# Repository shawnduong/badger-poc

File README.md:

# badger
Badger is a closed-source IoT RFID-based authentication, attendance tracking, 
notification, and punishmentx system for small to large scale events.

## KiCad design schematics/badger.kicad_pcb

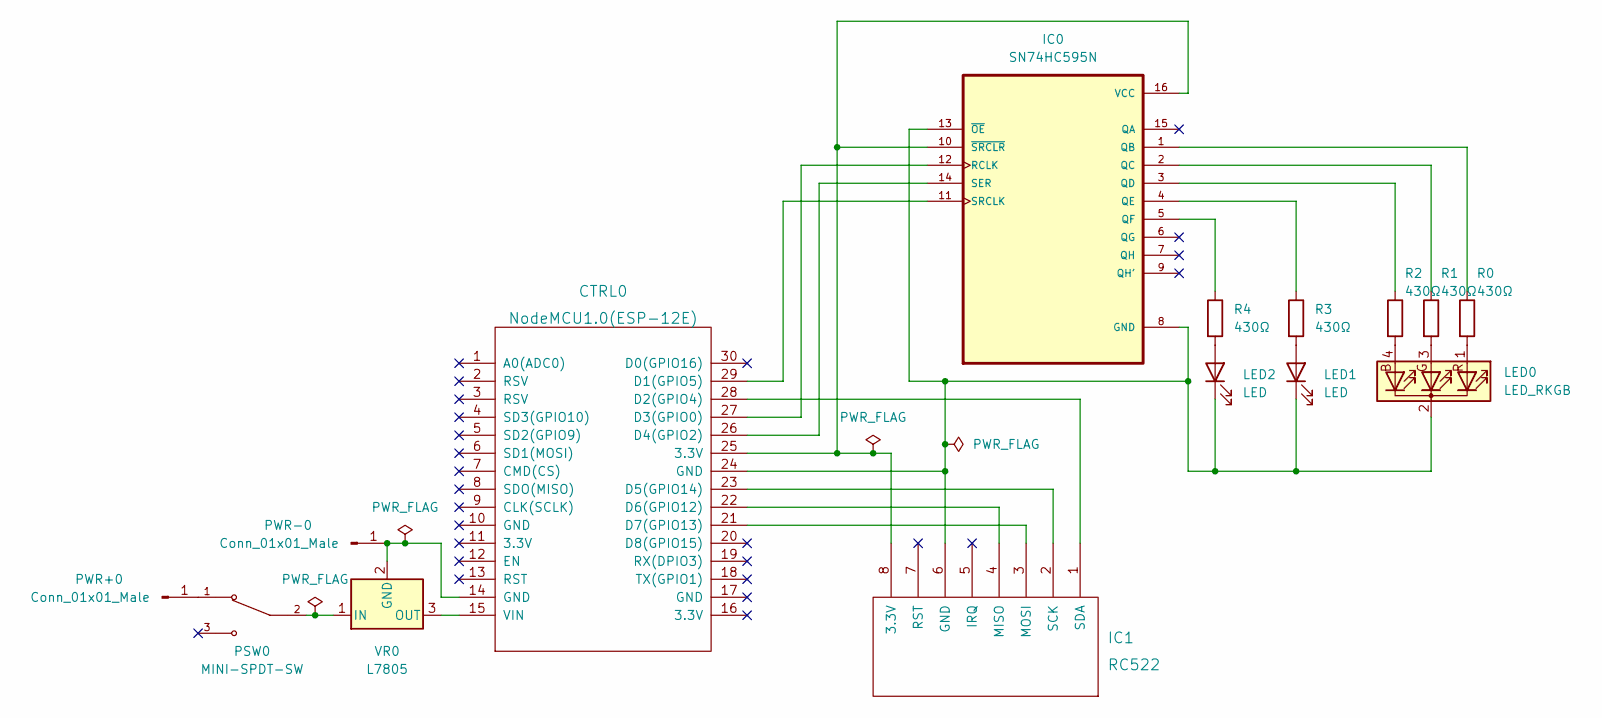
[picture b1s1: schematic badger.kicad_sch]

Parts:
CTRL0: NodeMCU1.0(ESP-12E); NodeMCU-LoLinV3
IC0: SN74HC595N; DIP794W45P254L1969H508Q16
IC1: RC522; rfid-rc522
LED0: LED_RKGB; LED_D5.0mm-4_RGB_Wide_Pins
LED1, LED2: LED; LED_D5.0mm
PSW0: MINI-SPDT-SW; SW_MINI-SPDT-SW; PARTREV C
PWR+0: Conn_01x01_Male; TestPoint_Pad_D2.0mm
PWR-0: Conn_01x01_Male; TestPoint_Pad_D2.0mm
R0, R1, R2, R3, R4: 430Ω; R_Axial_DIN0204_L3.6mm_D1.6mm_P7.62mm_Horizontal
VR0: L7805; TO-220-3_Vertical

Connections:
unnamed: CTRL0.14 (GND), PWR-0.1, VR0.2 (GND)
unnamed: CTRL0.15 (VIN), VR0.3 (OUT)
unnamed: CTRL0.21 (D7(GPIO13)), IC1.3 (MOSI)
unnamed: CTRL0.22 (D6(GPIO12)), IC1.4 (MISO)
unnamed: CTRL0.23 (D5(GPIO14)), IC1.2 (SCK)
unnamed: CTRL0.24 (GND), IC0.8 (GND), IC0.13 (~OE), IC1.6 (GND), LED0.2 (K), LED1.1 (K), LED2.1 (K)
unnamed: CTRL0.25 (3.3V), IC0.10 (~SRCLR), IC0.16 (VCC), IC1.8 (3.3V)
unnamed: CTRL0.26 (D4(GPIO2)), IC0.14 (SER)
unnamed: CTRL0.27 (D3(GPIO0)), IC0.12 (RCLK)
unnamed: CTRL0.28 (D2(GPIO4)), IC1.1 (SDA)
unnamed: CTRL0.29 (D1(GPIO5)), IC0.11 (SRCLK)
unnamed: IC0.1 (QB), R0.1
unnamed: IC0.2 (QC), R1.1
unnamed: IC0.3 (QD), R2.1
unnamed: IC0.4 (QE), R3.1
unnamed: IC0.5 (QF), R4.1
unnamed: LED0.1 (RA), R0.2
unnamed: LED0.3 (GA), R1.2
unnamed: LED0.4 (BA), R2.2
unnamed: LED1.2 (A), R3.2
unnamed: LED2.2 (A), R4.2
unnamed: PSW0.1, PWR+0.1
unnamed: PSW0.2, VR0.1 (IN)

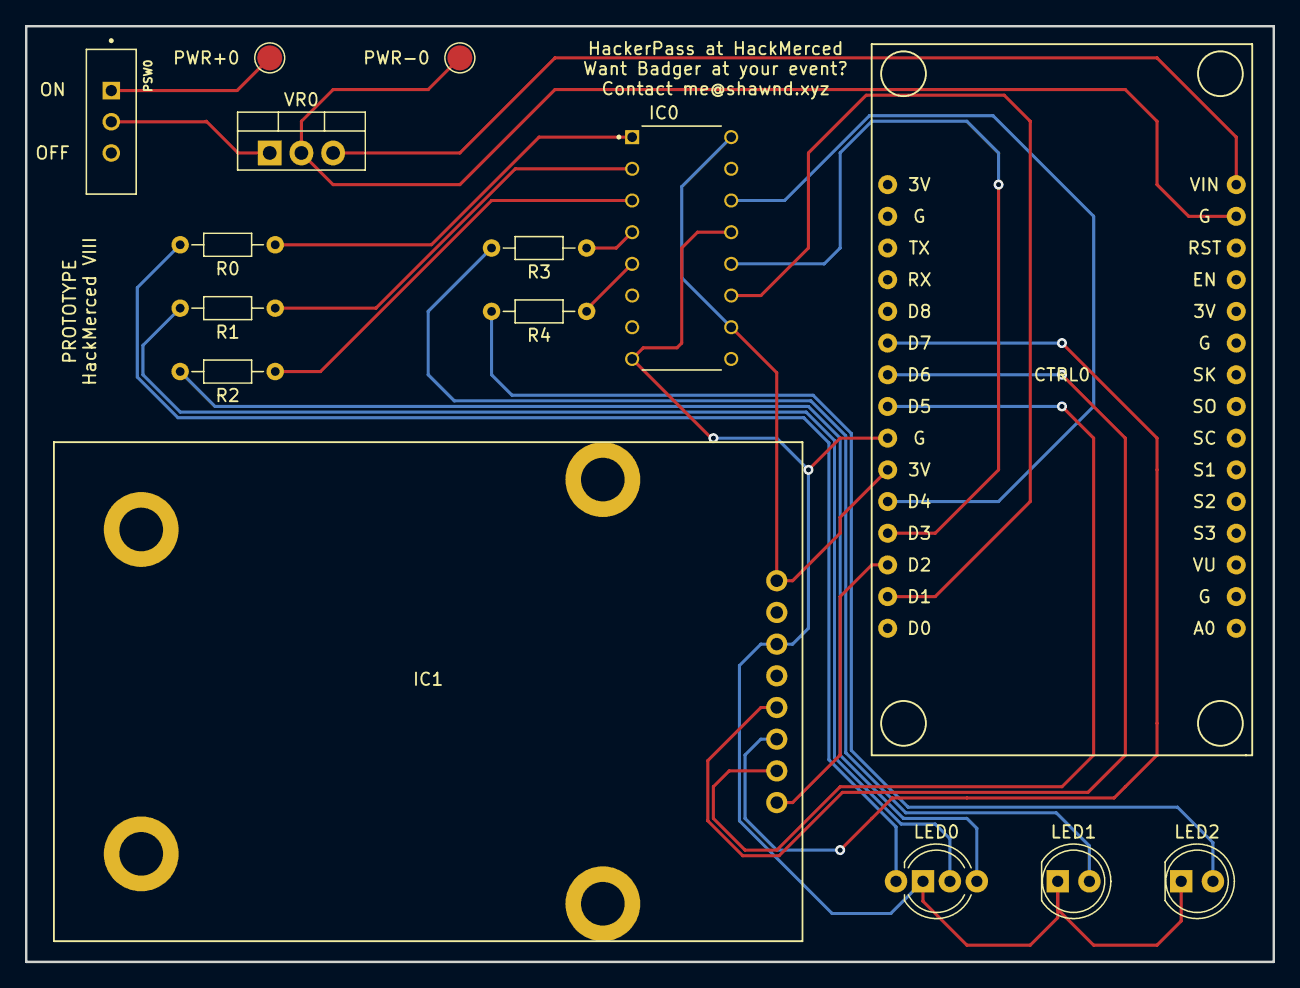
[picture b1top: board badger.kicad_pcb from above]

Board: 2 copper layers, 100.0 x 75.0 mm, 15 parts (0 on the bottom side), 23 nets.

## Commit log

2023-02-13 Initial commit.
2023-02-13 Implemented user management.
2023-02-13 Clarified a docstring and removed an unused template.
2023-02-13 Updated admin password and user table styling.
2023-02-13 Implemented user name/email setting.
2023-02-15 Added basic section headers for the user portal.
2023-02-15 Modularized API code.
2023-02-15 Added authorization clarifying comments to user API.
2023-02-15 Stylistic changes to JS.
2023-02-15 Minor formatting change (unused space).
2023-02-15 Implemented announcement creation and deletion.
2023-02-15 Removed text decoration from back links.
2023-02-15 Implemented user recent announcement view.
2023-02-15 Shrunk badger logo for admin and login screens.
2023-02-15 Implemented user announcement expansion toggle.
2023-02-15 Implemented announcement editing.
2023-02-15 Implemented announcement author preview.
2023-02-15 Added page titles.
2023-02-15 Fixed unterminated span.
2023-02-15 Removed card ID.
2023-02-16 Created event creation page.
2023-02-16 Fixed location not showing in event creation page preview.
2023-02-16 Prevented page refresh deleting form upon cancelling announcement.
2023-02-16 Implemented event creation API.
2023-02-16 Implemented event management list view.
2023-02-16 Implemented event deletion.
2023-02-16 Sorted events chronologically.
2023-02-16 Implemented color coding event table based on status.
2023-02-16 Implemented edit screen autofill.
2023-02-16 Fixed event list inefficiency bug.
2023-02-16 Added missing HTML end tags.
2023-02-16 Fixed missing div end tag.
2023-02-16 Fixed datetime-local autofill on Firefox.
2023-02-16 Fixed announcement edit cancel wiping progress.
2023-02-16 Implemented event edit JS.
2023-02-16 Implemented event edit API.
2023-02-16 Fixed unterminated div.
2023-02-16 Implemented event pages.
2023-02-16 Changed collapse text.
2023-02-16 Implemented event UI expand/collapse.
2023-02-16 Implemented code creation and deletion.
2023-02-16 Implemented code redemption.
2023-02-16 Added stamp section.
2023-02-17 Implemented stamp card.
2023-02-17 Removed legacy project name.
2023-02-17 Refactored security.
2023-02-17 Moved default account creation to security.
2023-02-17 Refactored Account.
2023-02-17 Corrected form item name.
2023-02-17 Refactored Event.
2023-02-17 Refactored Attendance.
2023-02-17 Refactored Code.
2023-02-17 Added check nonexistence check to Attendance.
2023-02-17 Refactored Submit.
2023-02-17 Light formatting edits and created Prize table.
2023-02-17 Created Redemption table.
2023-02-17 Refactored Punch.
2023-02-17 Refactored Announcement.
2023-02-17 Modularized models.
2023-02-17 Moved Flask key to app.
2023-02-17 Made null weblink empty instead of None.
2023-02-17 Modularized routes.
2023-02-17 Changed legacy Account attribute name.
2023-02-17 Fixed logout.
2023-02-17 Added include header to all pages.
2023-02-17 Refactored password change.
2023-02-17 Condensed front-end password change code.
2023-02-17 Refactored admin announcement views.
2023-02-17 Refactored Announcement API.
2023-02-17 Removed unused parameter in common announcement JS.
2023-02-17 Moved create announcement code.
2023-02-17 Made form names more dense.
2023-02-18 Created firmware test code.
2023-02-18 Added schematics.
2023-02-18 Refactored Events.
2023-02-18 Refactored Codes.
2023-02-18 Refactored Stamps.
2023-02-18 Renamed Prize to Reward.
2023-02-18 Implemented Rewards.
2023-02-18 Refactored user Accounts.
2023-02-18 Removed admin warning message.
2023-02-19 Fixed user view account info and badge info.
2023-02-19 Fixed user view events.
2023-02-19 Fixed user view announcements.
2023-02-19 Implemented Stamps view.
2023-02-19 Implemented reward claiming.
2023-02-19 Fixed bad event page title.
2023-02-19 Subtracted prize value from user account.
2023-02-19 Used common function for timestamp generation in event pages.
2023-02-19 Implemented reward limit one.
2023-02-19 Created test database.
2023-02-19 Renamed ino to firmware.
2023-02-19 Removed old config.
2023-02-19 Created example firmware config file.
2023-02-19 Corrected colors in led header.
2023-02-19 Downgraded identity to 32-bit integers.
2023-02-19 Implemented Badger unit identification and approval process.
2023-02-19 Implemented Badger deletion.
2023-02-19 Changed network test response LED to status LED.
2023-02-19 Changed network connection LED to status LED for clarity.
2023-02-19 Tweaked POST diag output.
2023-02-19 Implemented deep sleep and scanning.
2023-02-19 Printed MAC address to serial for whitelisting.
2023-02-19 Changed deep sleep to light sleep.
2023-02-20 Implemented Badger last seen.
2023-02-20 Implemented Badger configuration.
2023-02-20 Implemented Badger config preselection.
2023-02-20 Implemented Badger device healthcheck.
2023-02-20 Changed healthcheck to be able to not pass.
2023-02-20 Implemented Attendance scanning.
2023-02-21 Added Badger idle option.
2023-02-21 Fixed negative UID bug.
2023-02-21 Implemented provisionment.
2023-02-21 Added cooldown to Stamps.
2023-02-21 Implemented stamping.
2023-02-21 Updated test database.
2023-02-21 Fixed Stamps.
2023-02-21 Added logic for out of stamps.
2023-02-21 Implemented Punch view.
2023-02-21 Implemented admin-side redemption deletion.
2023-02-21 Implemented rewards claiming.
2023-02-21 Implemented points breakdown.
2023-02-21 Fixed sleep mode for power savings.
2023-02-21 Implemented locator system.
2023-03-03 Indentation for Windows error fix.
2023-03-03 Added pycache and instance database to gitignore.
2023-03-03 Imported Google Fonts: Alfa Slab One, Space Mono and Unbounded.
2023-03-03 Added CSS styling for user information module.
2023-03-03 Added styling for announcements module, reduced margins on mobile for responsiveness, minor JS edits for styling.
2023-03-03 Added styling to the schedule table and reformatted all modules to fit containers.
2023-03-03 Adapted default Badger login page to HackerPass.
2023-03-03 Made minor changes to title styling.
2023-03-03 Added stamp image for food distribution.
2023-03-03 Updated favicon to HackMerced tower.
2023-03-04 Microsoft Forever
